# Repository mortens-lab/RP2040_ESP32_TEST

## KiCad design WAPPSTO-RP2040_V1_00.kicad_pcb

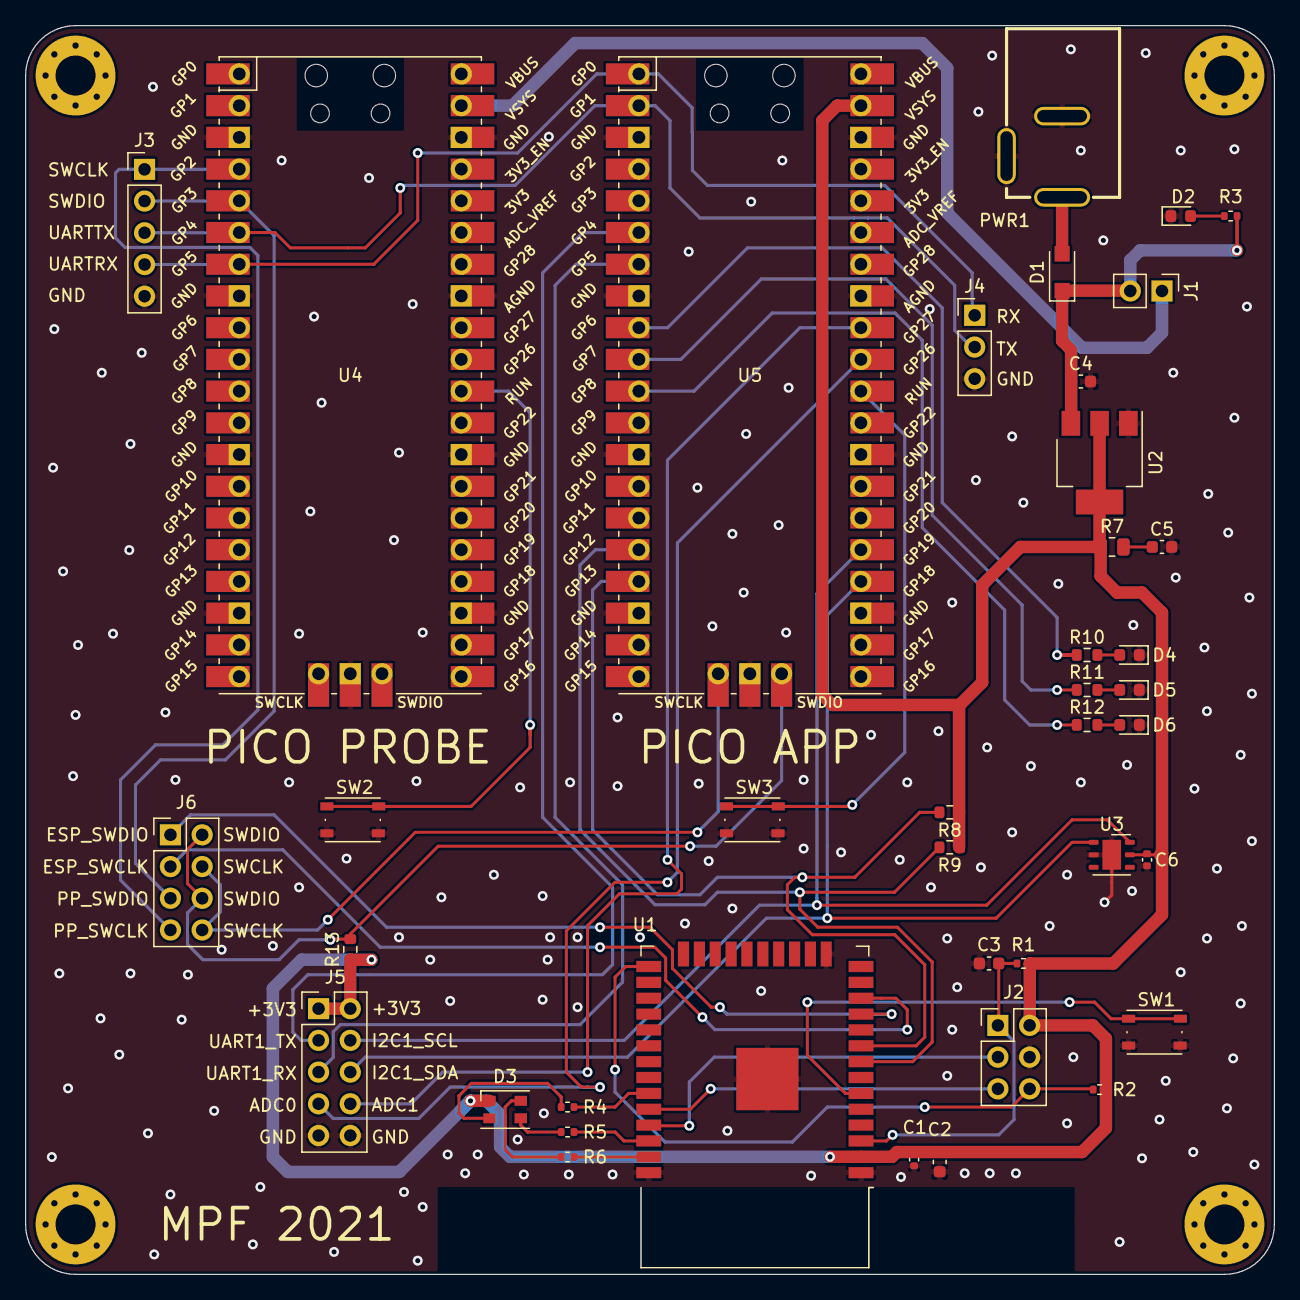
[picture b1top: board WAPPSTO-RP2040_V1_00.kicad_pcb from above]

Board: 2 copper layers, 100.0 x 100.0 mm, 44 parts (0 on the bottom side), 42 nets.

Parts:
C1, C6: 100n; C_0402_1005Metric
C2, C3: 1u; C_0603_1608Metric
C4, C5: 22u; C_0603_1608Metric
D1: MBR120; MBR120_SOD-123
D2: GREEN; LED_0603_1608Metric
D3: CLV1L-FKB; LED_Cree-PLCC4_3.2x2.8mm_CCW
D4, D5, D6: Y; LED_0603_1608Metric
H1, H2, H3, H4: MountingHole; MountingHole_3.2mm_M3_Pad_Via
J1: HEADER 2X1; PinHeader_1x02_P2.54mm_Vertical
J2: HEADER 3X2; PinHeader_2x03_P2.54mm_Vertical
J3: HEADER 5X1; PinHeader_1x05_P2.54mm_Vertical
J4: HEADER 3X1; PinHeader_1x03_P2.54mm_Vertical
J5: HEADER 5X2; PinHeader_2x05_P2.54mm_Vertical
J6: HEADER 4X2; PinHeader_2x04_P2.54mm_Vertical
PWR1: PWR-JAKPWR_JACK_UNI_MILLING; PWRJ-2mm(YDJ-1136)
R1, R2, R3, R4, R5, R6: 1K; R_0402_1005Metric
R7: 0.47R; R_0805_2012Metric
R8, R9, R13: 4k7; R_0603_1608Metric
R10, R11, R12: 1K; R_0603_1608Metric
SW1, SW2, SW3: SW_Push; SW_Push_1P1T_NO_Vertical_Wuerth_434133025816
U1: ESP32-WROOM-32D; ESP32-WROOM-32
U2: LM1117-3.3; SOT-223-3_TabPin2
U3: Si7021-A20; DFN-6-1EP_3x3mm_P1mm_EP1.5x2.4mm
U4, U5: Pico; RPi_Pico_SMD_TH

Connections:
+3V3: C1.1, C2.1, C6.1, D3.1, J2.2, J5.1, J5.2, R1.1, R2.1, R7.1, R8.1, R9.1, R13.1, U1.2, U2.2, U3.5, U5.39
+5V: C4.1, D1.1, J1.2, R3.1, U2.3
/ADC0: J5.7, U5.31
/ADC1: J5.8, U5.32
/ESP_EN: C3.1, J2.1, R1.2, U1.3
/ESP_IO0: J2.6, R2.2, U1.25
/ESP_RXD: J2.5, U1.34
/ESP_SWCLK: J6.3, U1.12
/ESP_SWDIO: J6.1, U1.11
/ESP_TXD: J2.3, U1.35
/I2C1_SCL: J5.4, U3.6, U5.25
/I2C1_SDA: J5.6, U3.1, U5.24
/I2C_SCL_RP: R8.2, U1.9, U5.17
/I2C_SDA_RP: R9.2, U1.8, U5.16
/LED0: R10.1, U5.9
/LED1: R11.1, U5.10
/LED2: R12.1, U5.11
/LED_BLUE: R6.2, U1.37
/LED_GREEN: R5.2, U1.36
/LED_RED: R4.2, U1.33
/PP_SWCLK: J3.1, J6.7, U4.4
/PP_SWDIO: J3.2, J6.5, U4.5
/SWCLK: J6.4, J6.8, U5.41
/SWDIO: J6.2, J6.6, R13.2, U5.43
/UART1_RX: J5.5, U5.7
/UART1_TX: J5.3, U5.6
/UART_RX: J3.4, J4.1, U4.7, U5.1
/UART_TX: J3.3, J4.2, U4.6, U5.2
GND: C1.2, C2.2, C3.2, C4.2, C5.2, C6.2, D2.1, D4.1, D5.1, D6.1, J2.4, J3.5, J4.3, J5.9, J5.10, PWR1.-, SW1.2, SW2.2, SW3.2, U1.1, U1.15, U1.38, U1.39, U2.1, U3.2, U3.7, U4.3, U4.8, U4.13, U4.18, U4.23, U4.28, U4.33, U4.38, U4.42, U5.3, U5.8, U5.13, U5.18, U5.23, U5.28, U5.33, U5.38, U5.42
unnamed: C5.1, R7.2
unnamed: D1.2, PWR1.+
unnamed: D2.2, R3.2
unnamed: D3.2, R4.1
unnamed: D3.3, R5.1
unnamed: D3.4, R6.1
unnamed: D4.2, R10.2
unnamed: D5.2, R11.2
unnamed: D6.2, R12.2
unnamed: SW1.1, U1.6
unnamed: SW2.1, U4.30
unnamed: SW3.1, U5.30
VCC: J1.1, U4.39
